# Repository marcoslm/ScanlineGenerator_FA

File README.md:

# VGA Scanline Generator

Este proyecto fue diseñado en 2015 para **Factory Arcade** ([sitio web](https://www.factoryarcade.es/)), una empresa dedicada a la restauración y fabricación de máquinas recreativas arcade. El objetivo es simular scanlines CRT en pantallas LCD. A diferencia de otros "slg" similares, este modelo soporta resoluciones **SVGA/XGA**.

## Características

- Alimentación desde el conector VGA de entrada o mediante el conector JP1 con una alimentación estabilizada de 5V DC.
- Soporta resoluciones VGA, SVGA y XGA, proporcionando una simulación fiel de las líneas de barrido.
- Sin lag de ninguna clase.

En este repositorio encontrarás los archivos de diseño en formato Eagle y los archivos Gerber listos para enviar a fabricación.

## Conectores y Jumpers de Configuración

| Conector/Jumper | Nombre      | Descripción |
|-----------------|-------------|-------------|
| CON1            | VGA OUT     | Salida VGA hacia el monitor |
| CON2            | VGA IN      | Entrada VGA desde la placa o PC arcade |
| JP1             | +5V         | Alimentación opcional de 5V DC |
| JP2             | ON/OFF      | 1-2: scanlines activas, 2-3: scanlines desactivadas |
| JP3             | POLARITY    | Polaridad de las señales de sincronización (según entrada) |
| JP4             | WIDTH       | Selección del grosor del scanline (fino o grueso) |
| JP5             | EVEN/ODD    | Selección de scanlines en líneas pares o impares del trazado |

## Solución de Problemas

Si al conectarlo todo tienes problemas de imagen:
- Verifica la configuración de la polaridad (JP3).
- Es posible que la señal de 5V desde el conector VGA IN sea insuficiente o inexistente. En ese caso, puedes alimentar la placa directamente a través de JP1 con 5V DC regulados.

## Rework en la Versión 1a

En esta primera versión del diseño, hay un pequeño error debido a la falta de una resistencia pull-down en el jumper JP2. Para corregirlo, deberás soldar una resistencia de 10k de forma manual.

## Bill of Materials (BOM)

Puedes consultar la lista de materiales completa en el archivo [`BOM.md`](./BOM.md).

## Licencia

Este proyecto se distribuye bajo la licencia **Creative Commons Attribution-NonCommercial 4.0 International (CC BY-NC 4.0)**. Se publica con el consentimiento de **Factory Arcade** y eres libre de utilizar, modificar y distribuir el trabajo, siempre otorgando el crédito adecuado y no está permitido el uso comercial del proyecto. Consulta el archivo [LICENSE](./LICENSE) para más detalles.

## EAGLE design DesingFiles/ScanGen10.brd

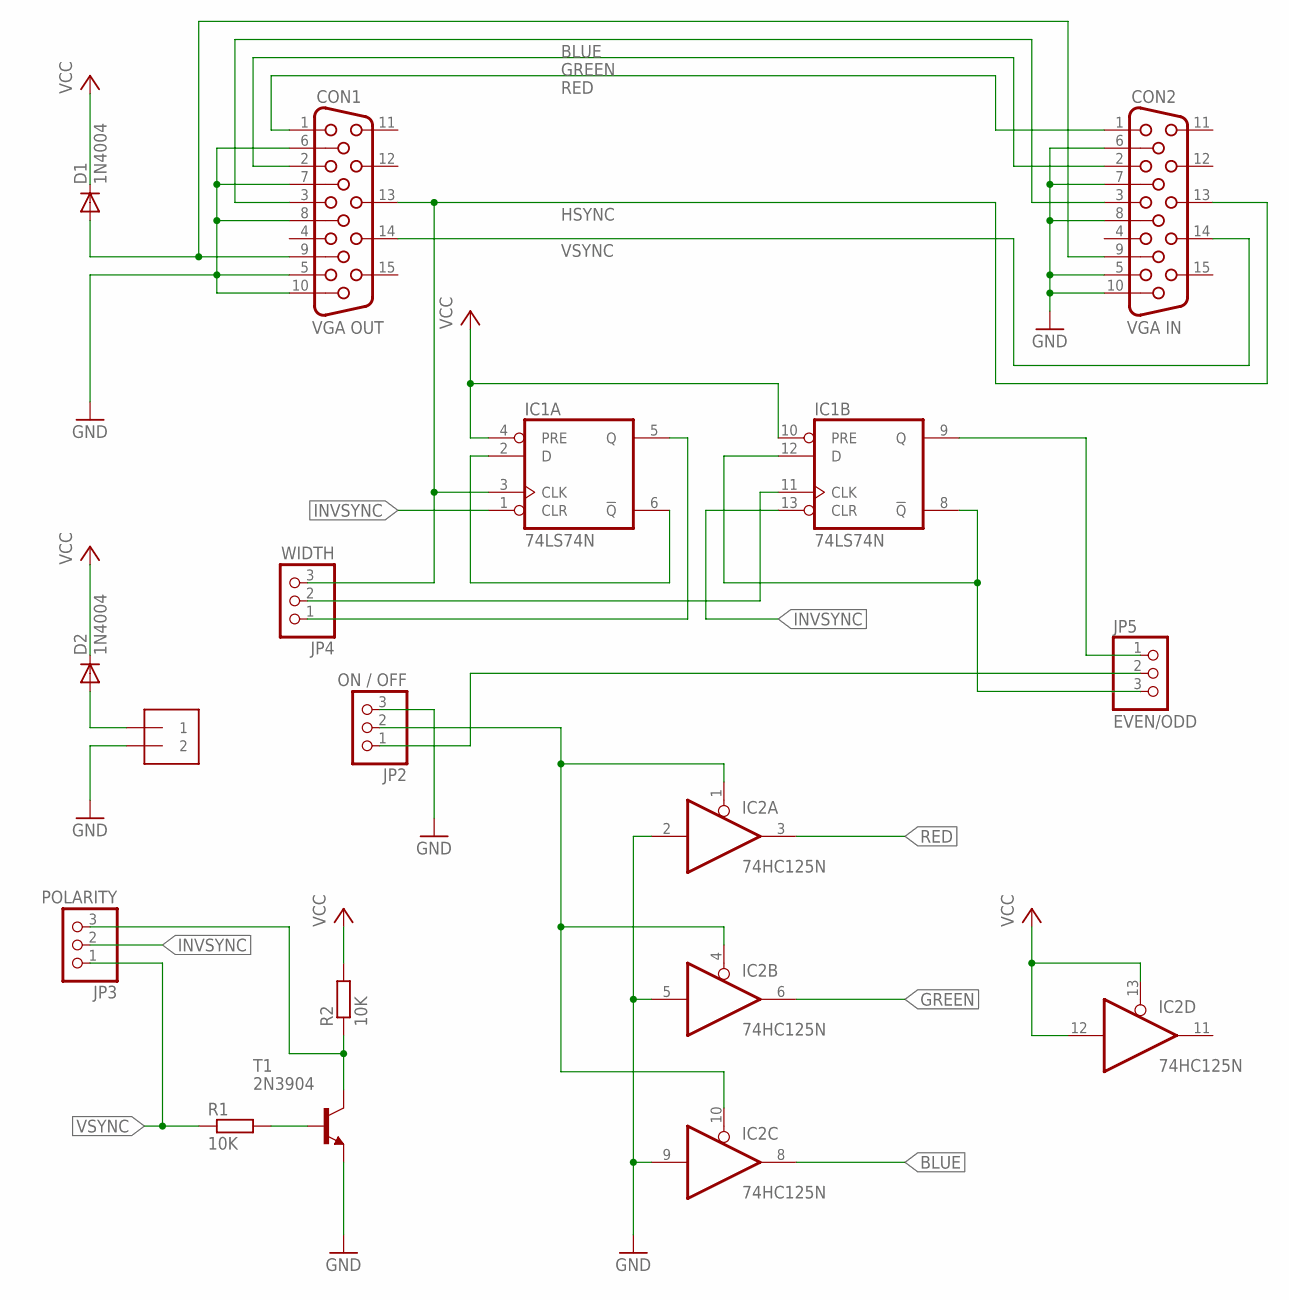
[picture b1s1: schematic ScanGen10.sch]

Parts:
CON1: VGA OUT; HDF15H
CON2: VGA IN; HDF15H
D1, D2: 1N4004; DO41-10
IC1: 74LS74N; DIL14
IC2: 74HC125N; DIL14
JP1: + 5V -; 1X2-3.5MM
JP2: ON / OFF; 1X03
JP3: POLARITY; 1X03
JP4: WIDTH; 1X03
JP5: EVEN/ODD; 1X03
R1, R2: 10K; 0204/7
T1: 2N3904; TO92

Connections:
BLUE: CON1.3, CON2.3, IC2.8 (O)
GND: CON1.5, CON1.6, CON1.7, CON1.8, CON1.10, CON2.5, CON2.6, CON2.7, CON2.8, CON2.10, IC1.7 (GND), IC2.2 (I), IC2.5 (I), IC2.7 (GND), IC2.9 (I), JP1.2, JP2.3, T1.3 (E)
GREEN: CON1.2, CON2.2, IC2.6 (O)
HSYNC: CON1.13, CON2.13, IC1.3 (CLK), JP4.3
INVSYNC: IC1.1 (CLR), IC1.13 (CLR), JP3.2
unnamed: CON1.9, CON2.9, D1.A
unnamed: D2.A, JP1.1
unnamed: IC1.11 (CLK), JP4.2
unnamed: IC1.5 (Q), JP4.1
unnamed: IC1.2 (D), IC1.6 (!Q)
unnamed: IC1.8 (!Q), IC1.12 (D), JP5.3
unnamed: IC1.9 (Q), JP5.1
unnamed: IC2.1 (OE), IC2.4 (OE), IC2.10 (OE), JP2.2
unnamed: R1.2, T1.2 (B)
unnamed: JP3.3, R2.1, T1.1 (C)
unnamed: JP2.1, JP5.2
RED: CON1.1, CON2.1, IC2.3 (O)
VCC: D1.C, D2.C, IC1.4 (PRE), IC1.10 (PRE), IC1.14 (VCC), IC2.12 (I), IC2.13 (OE), IC2.14 (VCC), R2.2
VSYNC: CON1.14, CON2.14, JP3.1, R1.1

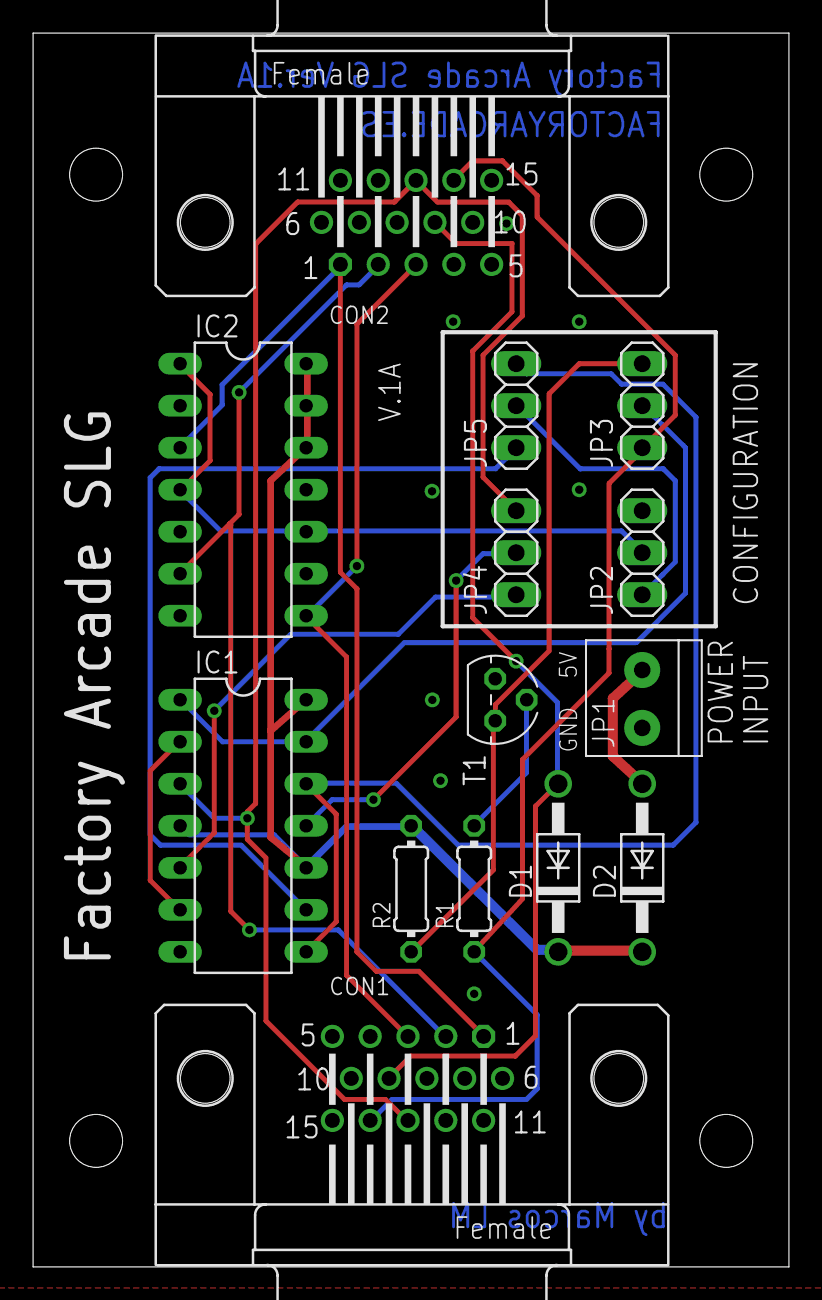
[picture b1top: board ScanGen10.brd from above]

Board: 2 copper layers, 45.7 x 74.6 mm, 14 parts (0 on the bottom side), 19 nets.

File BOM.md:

# Bill of Materials (BOM)

| Qty | Value   | Device        | Package  | Parts  | Description                                                         |
|-----|---------|---------------|----------|--------|---------------------------------------------------------------------|
| 1   | +5V -   | 1X2-3.5MM     | 1X2-3.5MM| JP1    | 3.5mm Terminal block                                                |
| 2   | 10K     | R-EU_0204/7   | 0204/7   | R1, R2 | RESISTOR, European symbol                                           |
| 2   | 1N4004  | 1N4004        | DO41-10  | D1, D2 | DIODE                                                               |
| 1   | 2N3904  | 2N3904        | TO92     | T1     | NPN TRANSISTOR                                                      |
| 1   | 74HC125N| 74HC125N      | DIL14    | IC2    | Quad bus BUFFER, 3-state                                            |
| 1   | 74LS74N | 74LS74N       | DIL14    | IC1    | Dual D type positive edge triggered FLIP FLOP, preset and clear      |
| 1   | EVEN/ODD| PINHD-1X3     | 1X03     | JP5    | PIN HEADER                                                          |
| 1   | ON / OFF| PINHD-1X3     | 1X03     | JP2    | PIN HEADER                                                          |
| 1   | POLARITY| PINHD-1X3     | 1X03     | JP3    | PIN HEADER                                                          |
| 1   | VGA IN  | HF15H         | HDF15H   | CON2   | SUB-D                                                               |
| 1   | VGA OUT | HF15H         | HDF15H   | CON1   | SUB-D                                                               |
| 1   | WIDTH   | PINHD-1X3     | 1X03     | JP4    | PIN HEADER                                                          |

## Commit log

2024-09-07 Commit inicial
2024-09-07 BOM en formato markdown
